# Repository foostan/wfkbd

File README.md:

# wfkbd
Waffle keyboard, a split ortholinear keyboard with 4 or 5x6 keys, based on [Helix](https://github.com/MakotoKurauchi/helix) and [Let's Split](https://github.com/climbalima/let-s-Split-v2).

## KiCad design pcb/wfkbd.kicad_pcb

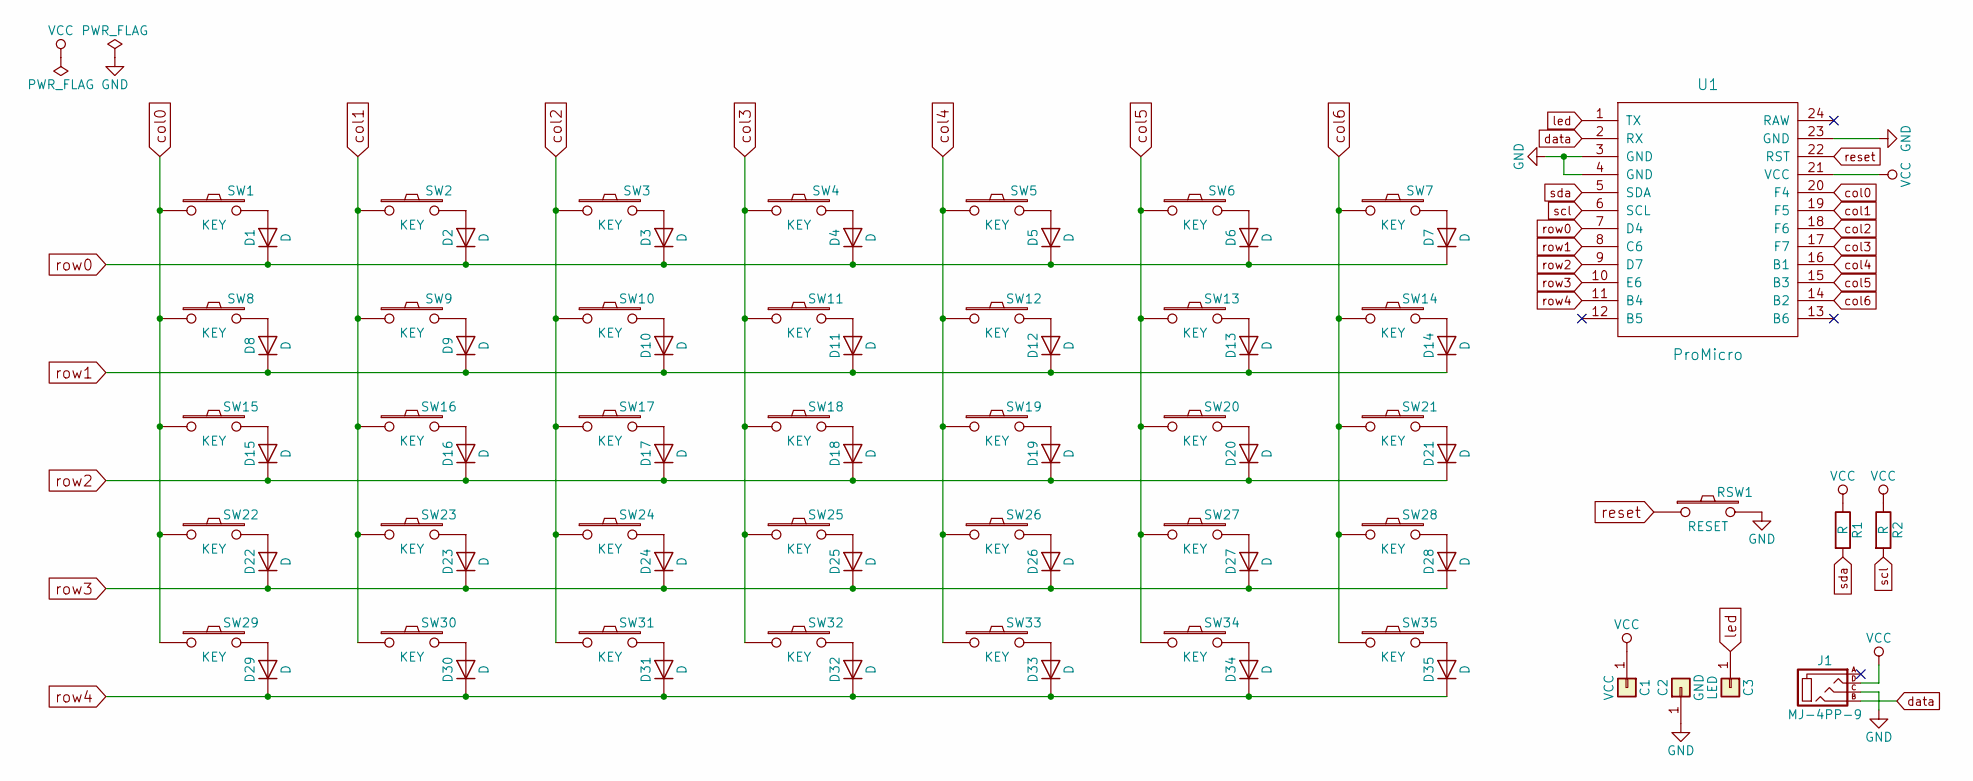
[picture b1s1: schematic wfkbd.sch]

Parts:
C1: VCC; 1pin_conn
C2: GND; 1pin_conn
C3: LED; 1pin_conn
D1, D2, D3, D4, D5, D6, D7, D8, D9, D10, D11, D12, D13, D14, D15, D16, D17, D18, D19, D20, D21, D22, D23, D24, D25, D26, D27, D28, D29, D30, D31, D32, D33, D34, D35: D; D3_TH_SMD
J1: MJ-4PP-9
R1, R2: R
RSW1: RESET; SW_Tactile_SPST_Angled_MJTP1117
SW1, SW2, SW3, SW4, SW5, SW6, SW7, SW8, SW9, SW10, SW11, SW12, SW13, SW14, SW15, SW16, SW17, SW18, SW19, SW20, SW21, SW22, SW23, SW24, SW25, SW26, SW27, SW28, SW29, SW30, SW31, SW32, SW33, SW34, SW35: KEY; MX_ALPS_PG1350_noLed
U1: ProMicro

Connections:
GND: C2.1, J1.C, RSW1.2, U1.3 (GND), U1.4 (GND), U1.23 (GND); also elsewhere on the board
unnamed: D1.2 (A), SW1.2
unnamed: D2.2 (A), SW2.2
unnamed: D3.2 (A), SW3.2
unnamed: D4.2 (A), SW4.2
unnamed: D5.2 (A), SW5.2
unnamed: D6.2 (A), SW6.2
unnamed: D7.2 (A), SW7.2
unnamed: D8.2 (A), SW8.2
unnamed: D9.2 (A), SW9.2
unnamed: D10.2 (A), SW10.2
unnamed: D11.2 (A), SW11.2
unnamed: D12.2 (A), SW12.2
unnamed: D13.2 (A), SW13.2
unnamed: D14.2 (A), SW14.2
unnamed: D15.2 (A), SW15.2
unnamed: D16.2 (A), SW16.2
unnamed: D17.2 (A), SW17.2
unnamed: D18.2 (A), SW18.2
unnamed: D19.2 (A), SW19.2
unnamed: D20.2 (A), SW20.2
unnamed: D21.2 (A), SW21.2
unnamed: D22.2 (A), SW22.2
unnamed: D23.2 (A), SW23.2
unnamed: D24.2 (A), SW24.2
unnamed: D25.2 (A), SW25.2
unnamed: D26.2 (A), SW26.2
unnamed: D27.2 (A), SW27.2
unnamed: D28.2 (A), SW28.2
unnamed: D29.2 (A), SW29.2
unnamed: D30.2 (A), SW30.2
unnamed: D31.2 (A), SW31.2
unnamed: D32.2 (A), SW32.2
unnamed: D33.2 (A), SW33.2
unnamed: D34.2 (A), SW34.2
unnamed: D35.2 (A), SW35.2
VCC: C1.1, J1.D, R1.1, R2.1, U1.21 (VCC); also elsewhere on the board
col0: SW1.1, SW8.1, SW15.1, SW22.1, SW29.1, U1.20 (F4)
col1: SW2.1, SW9.1, SW16.1, SW23.1, SW30.1, U1.19 (F5)
col2: SW3.1, SW10.1, SW17.1, SW24.1, SW31.1, U1.18 (F6)
col3: SW4.1, SW11.1, SW18.1, SW25.1, SW32.1, U1.17 (F7)
col4: SW5.1, SW12.1, SW19.1, SW26.1, SW33.1, U1.16 (B1)
col5: SW6.1, SW13.1, SW20.1, SW27.1, SW34.1, U1.15 (B3)
col6: SW7.1, SW14.1, SW21.1, SW28.1, SW35.1, U1.14 (B2)
data: J1.B, U1.2 (RX); also elsewhere on the board
led: C3.1, U1.1 (TX); also elsewhere on the board
reset: RSW1.1, U1.22 (RST); also elsewhere on the board
row0: D1.1 (K), D2.1 (K), D3.1 (K), D4.1 (K), D5.1 (K), D6.1 (K), D7.1 (K), U1.7 (D4)
row1: D8.1 (K), D9.1 (K), D10.1 (K), D11.1 (K), D12.1 (K), D13.1 (K), D14.1 (K), U1.8 (C6)
row2: D15.1 (K), D16.1 (K), D17.1 (K), D18.1 (K), D19.1 (K), D20.1 (K), D21.1 (K), U1.9 (D7)
row3: D22.1 (K), D23.1 (K), D24.1 (K), D25.1 (K), D26.1 (K), D27.1 (K), D28.1 (K), U1.10 (E6)
row4: D29.1 (K), D30.1 (K), D31.1 (K), D32.1 (K), D33.1 (K), D34.1 (K), D35.1 (K), U1.11 (B4)
scl: R2.2, U1.6 (SCL)
sda: R1.2, U1.5 (SDA)

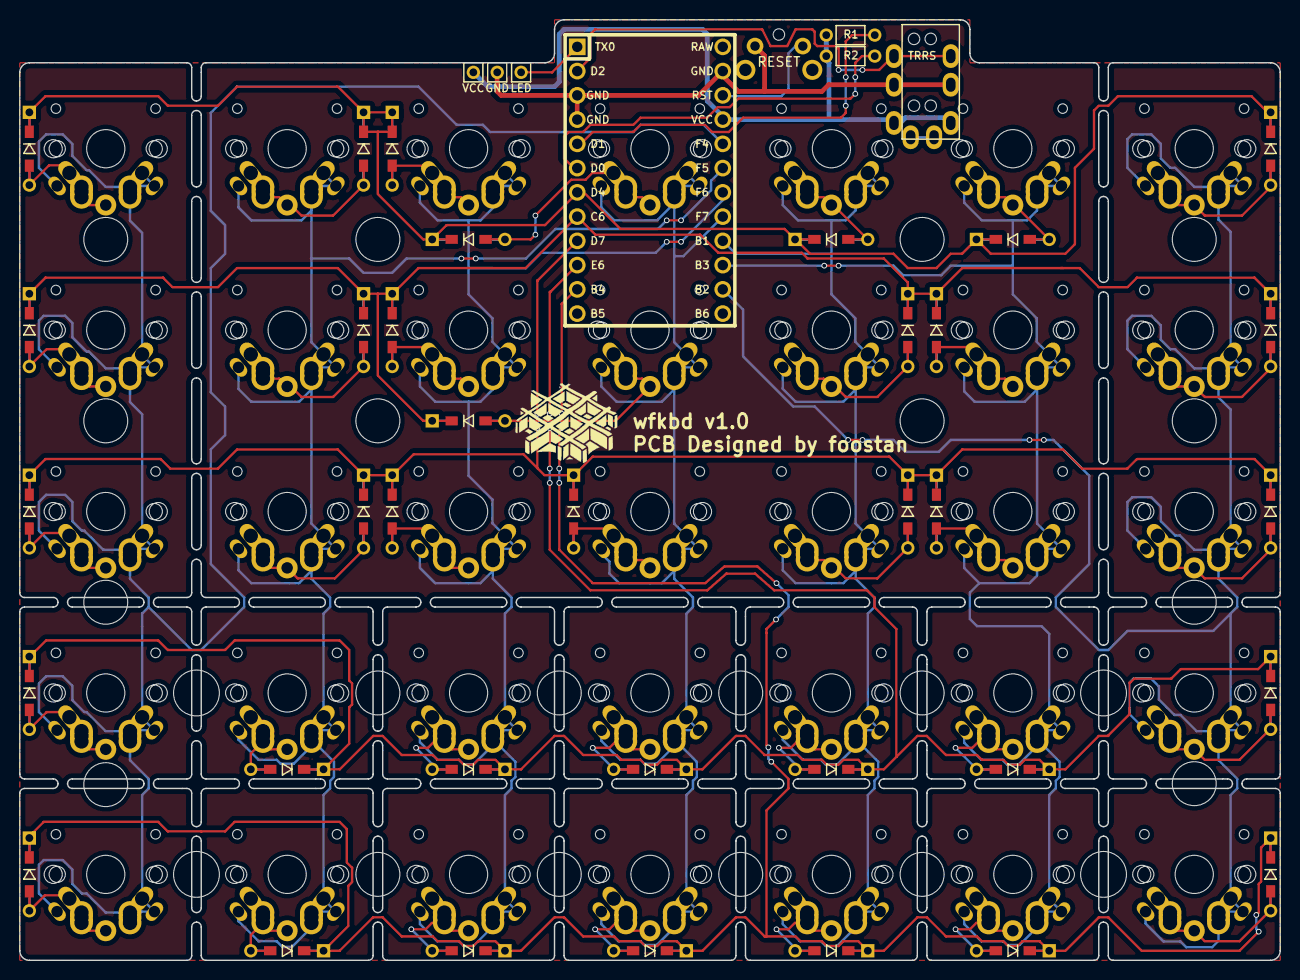
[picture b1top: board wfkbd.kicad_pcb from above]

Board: 2 copper layers, 132.0 x 98.5 mm, 78 parts (1 on the bottom side), 54 nets.

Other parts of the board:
GND: GND; 1pin_conn
LED: LED; 1pin_conn
RESET: RESET; SW_Tactile_SPST_Angled_MJTP1117
TRRS: MJ-4PP-9
VCC: VCC; 1pin_conn

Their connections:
GND: GND.1, RESET.2, TRRS.C; also elsewhere on the board
VCC: TRRS.D, VCC.1; also elsewhere on the board
data: TRRS.B; also elsewhere on the board
led: LED.1; also elsewhere on the board
reset: RESET.1; also elsewhere on the board

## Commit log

2018-03-25 Add README.md
2018-03-25 Add descriprions
2018-03-25 Initialize kicad
2018-03-25 Add base pro data
2018-03-25 Scalable cols/rows
2018-03-25 Add nets
2018-03-26 Add splid line
2018-03-29 Add pcbnew files
2018-03-29 Remove unused lines
2018-03-30 To simply
2018-03-30 Add holes
2018-03-30 To all green DRC
2018-03-30 Fix lines and add text of author
2018-03-31 Add waffle logo
2018-04-07 Add new case data
2018-04-10 Add *.bak to .gitignore
2018-04-10 Update case
2018-04-21 Update split lines
2018-04-22 Release v1.0
2019-06-30 Add GND filled zones (front & back)
2019-06-30 Add fill zone to back
